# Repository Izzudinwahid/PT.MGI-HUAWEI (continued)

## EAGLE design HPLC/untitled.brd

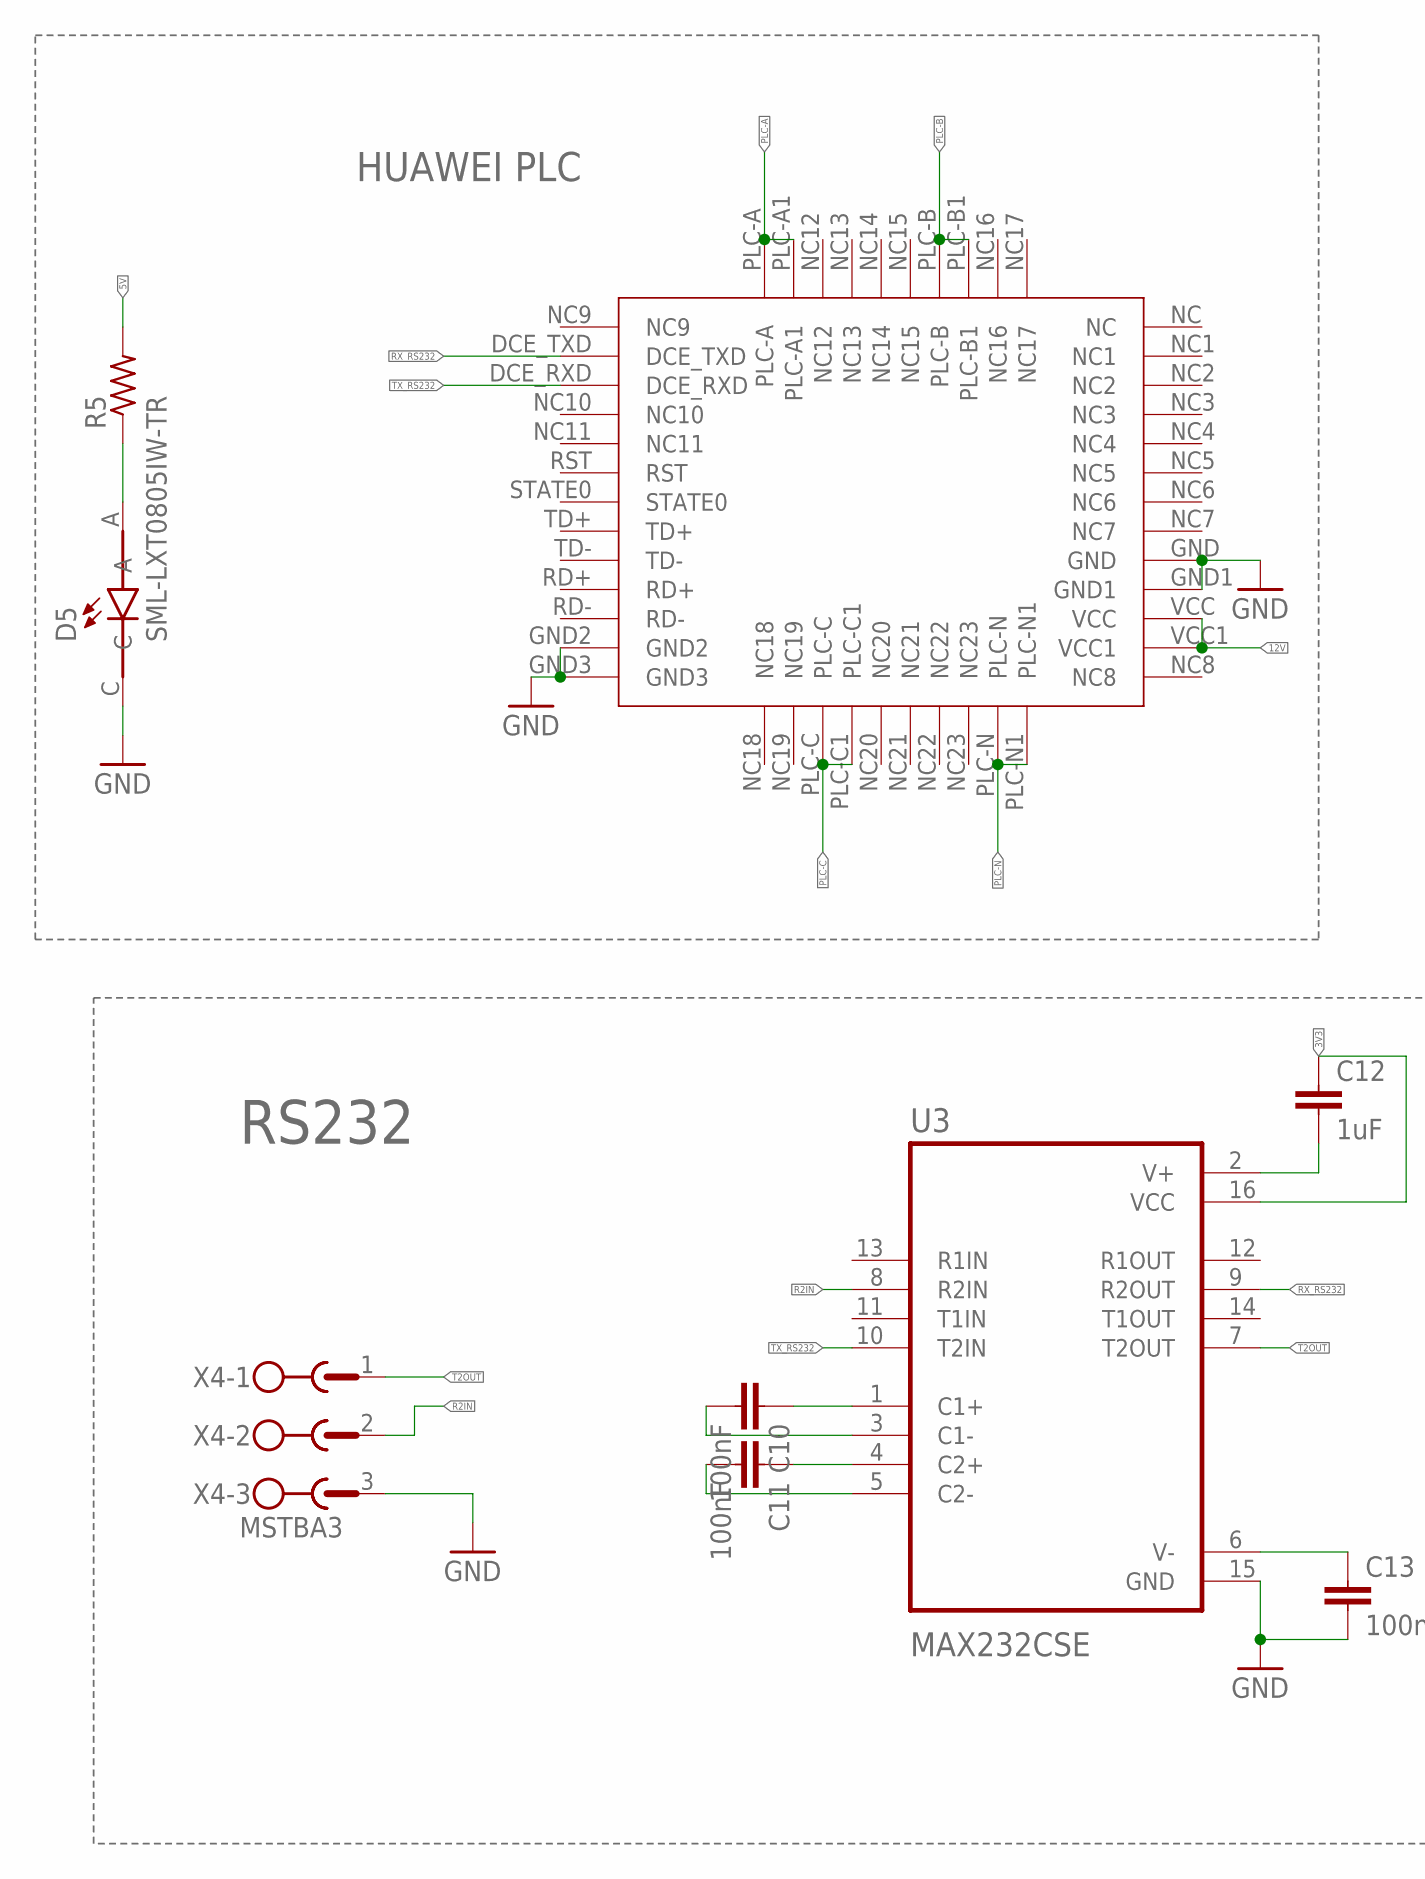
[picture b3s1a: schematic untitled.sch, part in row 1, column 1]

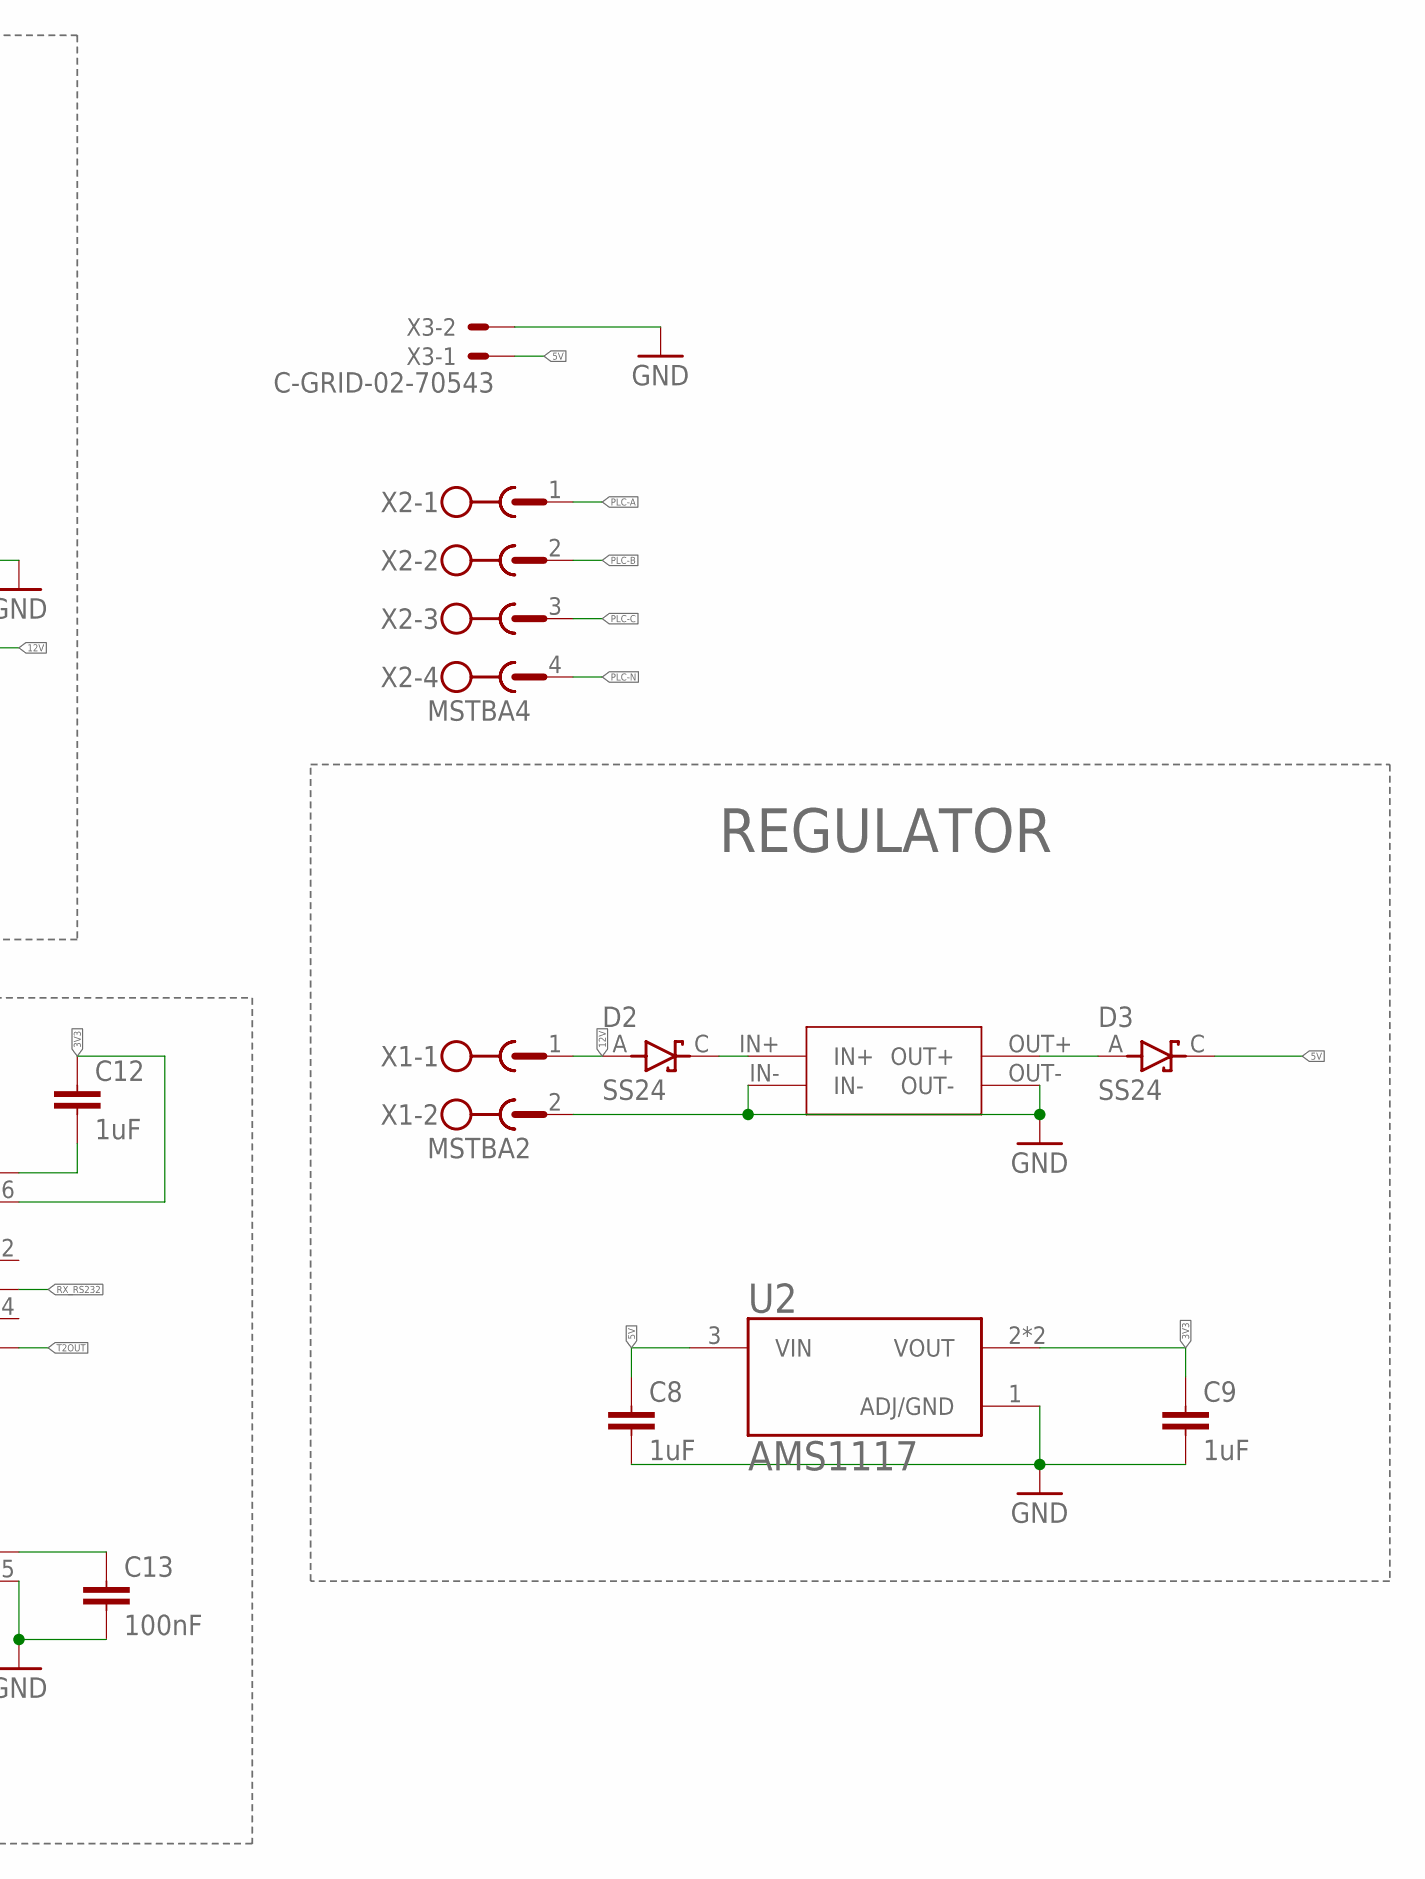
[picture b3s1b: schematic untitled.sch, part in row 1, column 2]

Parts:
C8, C9, C12: 1uF; C0805K
C10, C11, C13: 100nF; C0805K
D2, D3: SS24; DIOM5336X265N
D5: SML-LXT0805IW-TR; LEDC2012X120N
HUAWEI-PLC1: HUAWEI-PLC
MINI1: MINI560
R5: R-US_M0805; M0805
U2: AMS1117; SOT229P700X180-4N
U3: MAX232CSE; SOIC127P600X175-16N
X1: MSTBA2
X2: MSTBA4
X3: C-GRID-02-70543; 70543-02
X4: MSTBA3

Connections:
3V3: C9.1, C12.1, U2.2 (VOUT), U2.4 (VOUT), U3.16 (VCC)
5V: C8.1, D3.C (K), R5.2, U2.3 (VIN), X3.1
12V: D2.A, HUAWEI-PLC1.VCC, HUAWEI-PLC1.VCC1, X1.1
GND: C8.2, C9.2, C13.2, D5.C, HUAWEI-PLC1.GND, HUAWEI-PLC1.GND1, HUAWEI-PLC1.GND2, HUAWEI-PLC1.GND3, MINI1.IN-, MINI1.OUT-, U2.1 (ADJ/GND), U3.15 (GND), X1.2, X3.2, X4.3
unnamed: D2.C (K), MINI1.IN+
unnamed: D3.A, MINI1.OUT+
unnamed: C10.1, U3.1 (C1+)
unnamed: C10.2, U3.3 (C1-)
unnamed: C11.1, U3.4 (C2+)
unnamed: C11.2, U3.5 (C2-)
unnamed: C13.1, U3.6 (V-)
unnamed: C12.2, U3.2 (V+)
unnamed: D5.A, R5.1
PLC-A: HUAWEI-PLC1.PLC-A, HUAWEI-PLC1.PLC-A1, X2.1
PLC-B: HUAWEI-PLC1.PLC-B, HUAWEI-PLC1.PLC-B1, X2.2
PLC-C: HUAWEI-PLC1.PLC-C, HUAWEI-PLC1.PLC-C1, X2.3
PLC-N: HUAWEI-PLC1.PLC-N, HUAWEI-PLC1.PLC-N1, X2.4
R2IN: U3.8 (R2IN), X4.2
RX_RS232: HUAWEI-PLC1.DCE_TXD, U3.9 (R2OUT)
T2OUT: U3.7 (T2OUT), X4.1
TX_RS232: HUAWEI-PLC1.DCE_RXD, U3.10 (T2IN)

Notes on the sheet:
HUAWEI PLC
REGULATOR
RS232

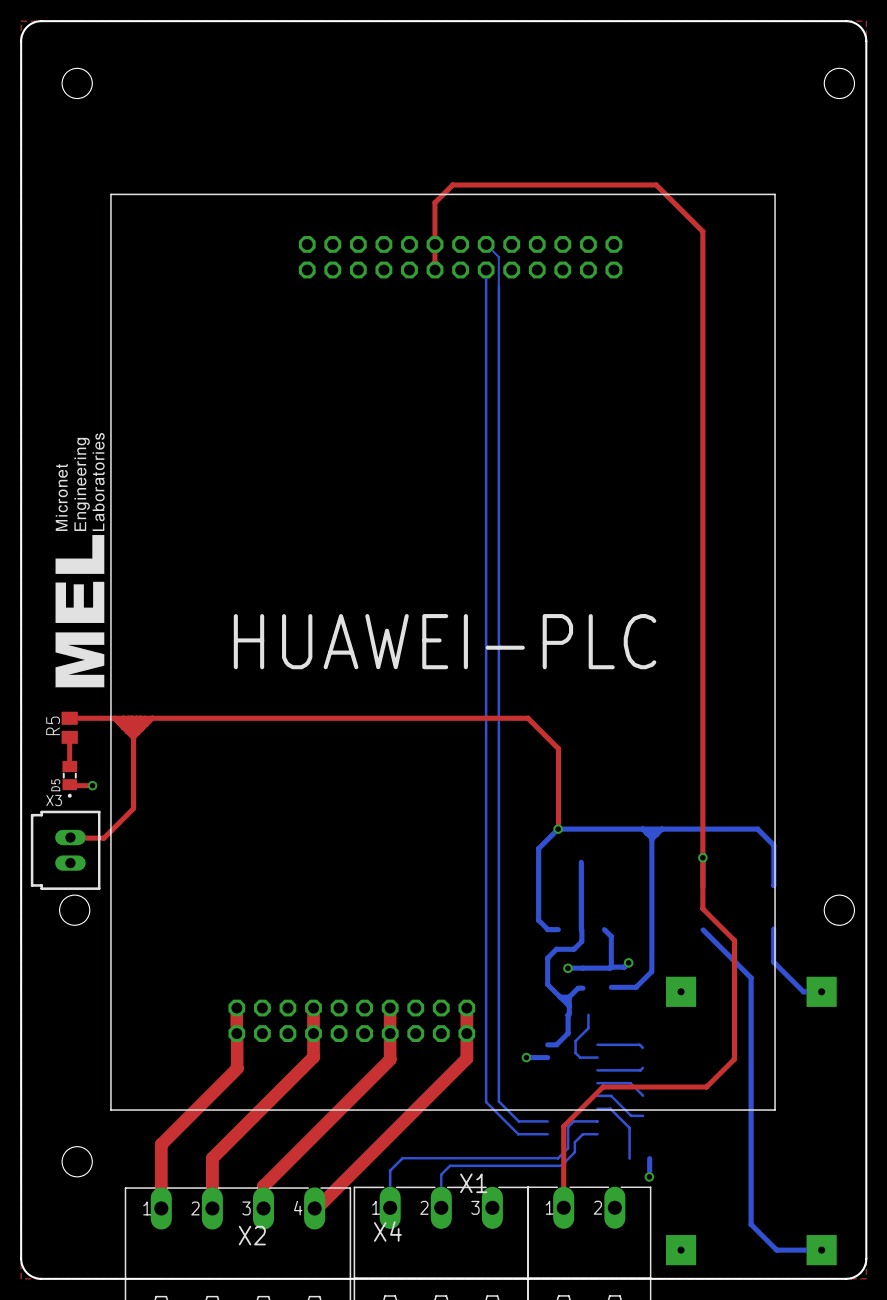
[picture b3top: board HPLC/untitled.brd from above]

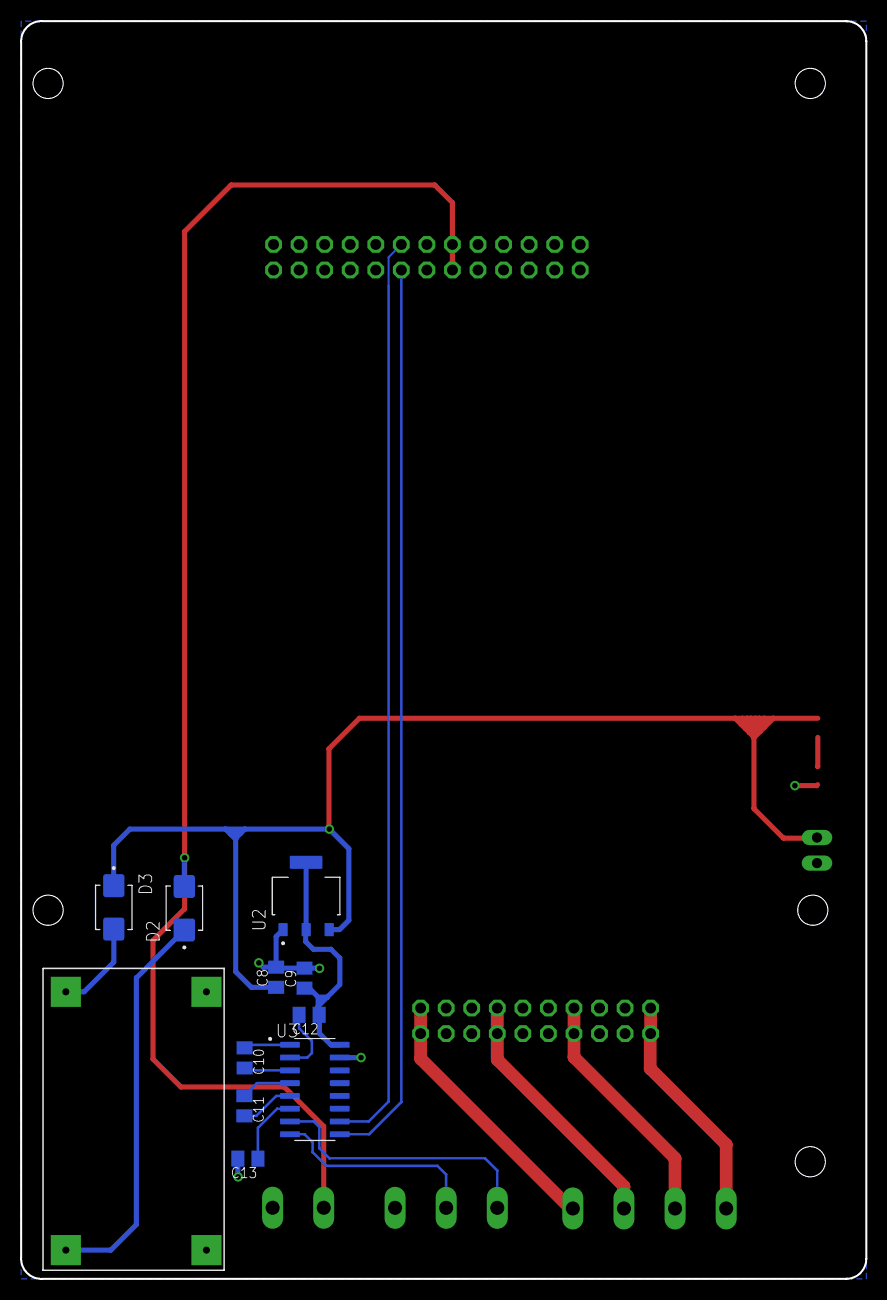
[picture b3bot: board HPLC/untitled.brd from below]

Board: 2 copper layers, 84.0 x 125.0 mm, 18 parts (11 on the bottom side), 21 nets.

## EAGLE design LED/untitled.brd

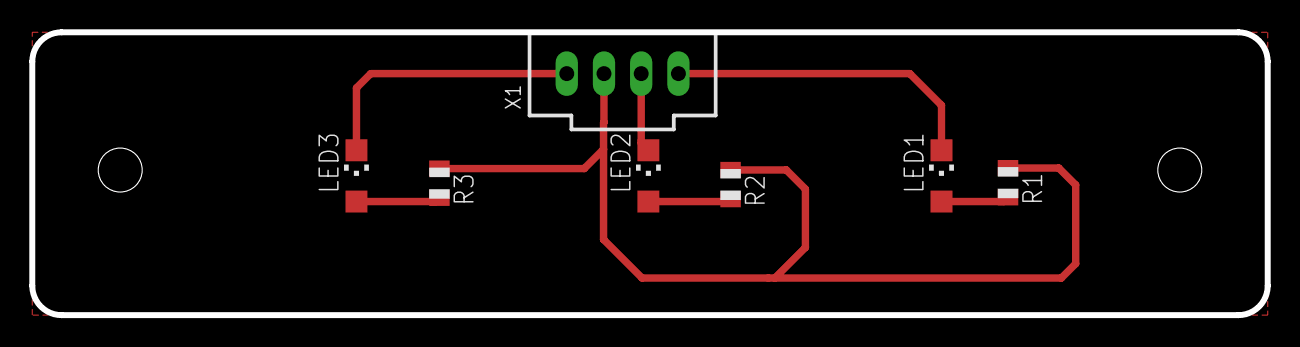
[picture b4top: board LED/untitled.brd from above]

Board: 2 copper layers, 84.3 x 19.3 mm, 7 parts (0 on the bottom side), 7 nets.

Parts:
LED1, LED2, LED3: CHIPLED_1206
R1, R2, R3: R0805
X1: C-GRID-04-70543; 70543-04

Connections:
GND: LED3.C, X1.1
unnamed: LED2.C, X1.3
unnamed: LED1.C, X1.4
unnamed: R1.1, R2.1, R3.1, X1.2
unnamed: LED1.A, R1.2
unnamed: LED2.A, R2.2
unnamed: LED3.A, R3.2

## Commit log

2024-07-02 PCB huawei
2024-07-02 revisi HPLC
2024-07-02 PCB SUPERCAP dan HPLC
2024-07-03 3 PCB done
2024-07-08 REVISI PCB Konektor
2024-07-15 tambahan PCB LED
2024-07-16 REVISI PCB LED
